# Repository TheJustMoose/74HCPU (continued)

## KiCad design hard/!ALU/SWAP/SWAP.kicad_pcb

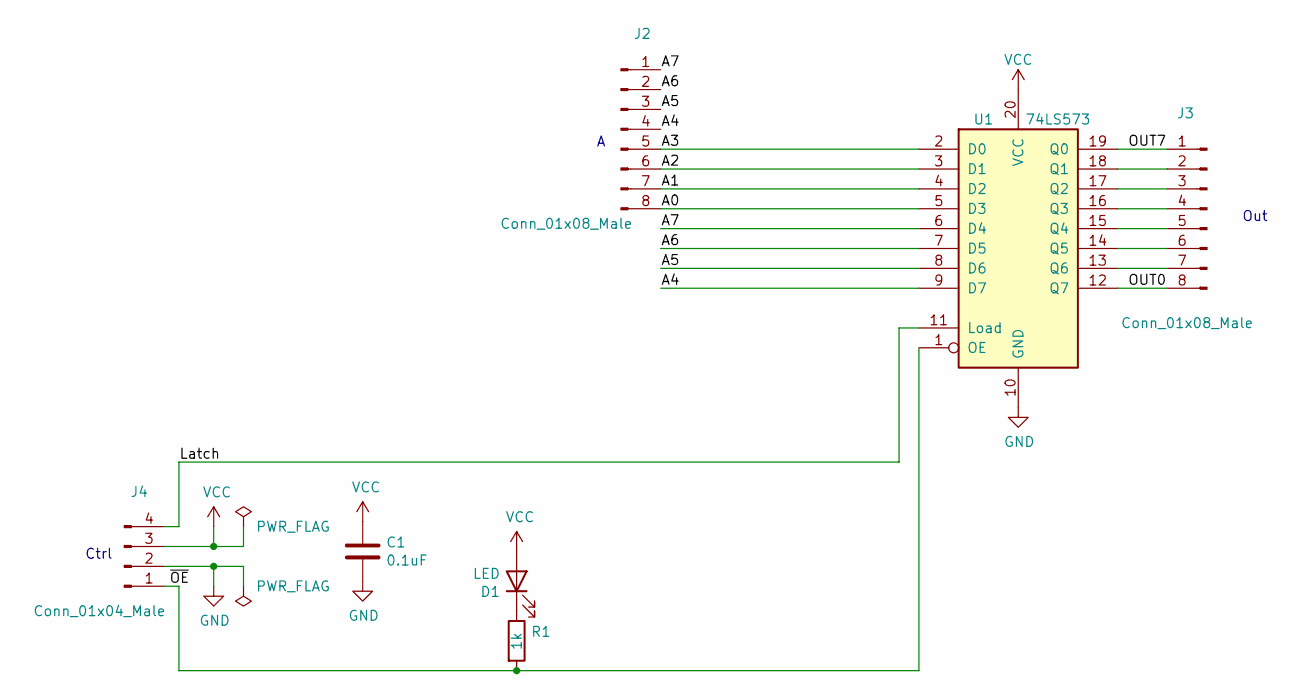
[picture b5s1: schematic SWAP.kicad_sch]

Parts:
C1: 0.1uF; C_0805_2012Metric_Pad1.18x1.45mm_HandSolder
D1: LED; LED_0805_2012Metric_Pad1.15x1.40mm_HandSolder
J2, J3: Conn_01x08_Male; PinHeader_1x08_P2.54mm_Horizontal
J4: Conn_01x04_Male; PinHeader_1x04_P2.54mm_Horizontal
R1: 1k; R_0805_2012Metric_Pad1.20x1.40mm_HandSolder
U1: 74LS573; SOP-20_7.5x12.8mm_P1.27mm

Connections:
/A0: J2.8, U1.5 (D3)
/A1: J2.7, U1.4 (D2)
/A2: J2.6, U1.3 (D1)
/A3: J2.5, U1.2 (D0)
/A4: J2.4, U1.9 (D7)
/A5: J2.3, U1.8 (D6)
/A6: J2.2, U1.7 (D5)
/A7: J2.1, U1.6 (D4)
/Latch: J4.4, U1.11 (Load)
/OUT0: J3.8, U1.12 (Q7)
/OUT7: J3.1, U1.19 (Q0)
/~OE: J4.1, R1.2, U1.1 (OE)
GND: C1.2, J4.2, U1.10 (GND)
unnamed: D1.1 (K), R1.1
unnamed: J3.2, U1.18 (Q1)
unnamed: J3.3, U1.17 (Q2)
unnamed: J3.4, U1.16 (Q3)
unnamed: J3.5, U1.15 (Q4)
unnamed: J3.6, U1.14 (Q5)
unnamed: J3.7, U1.13 (Q6)
VCC: C1.1, D1.2 (A), J4.3, U1.20 (VCC)

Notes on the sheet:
Out
Ctrl

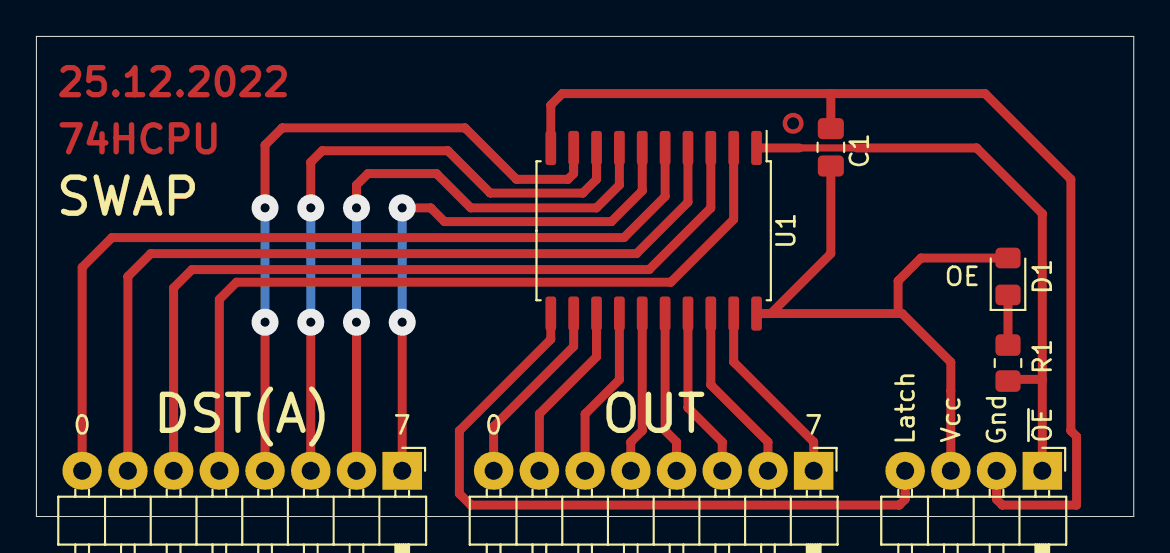
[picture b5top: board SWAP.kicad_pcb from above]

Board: 2 copper layers, 61.0 x 26.7 mm, 7 parts (0 on the bottom side), 21 nets.

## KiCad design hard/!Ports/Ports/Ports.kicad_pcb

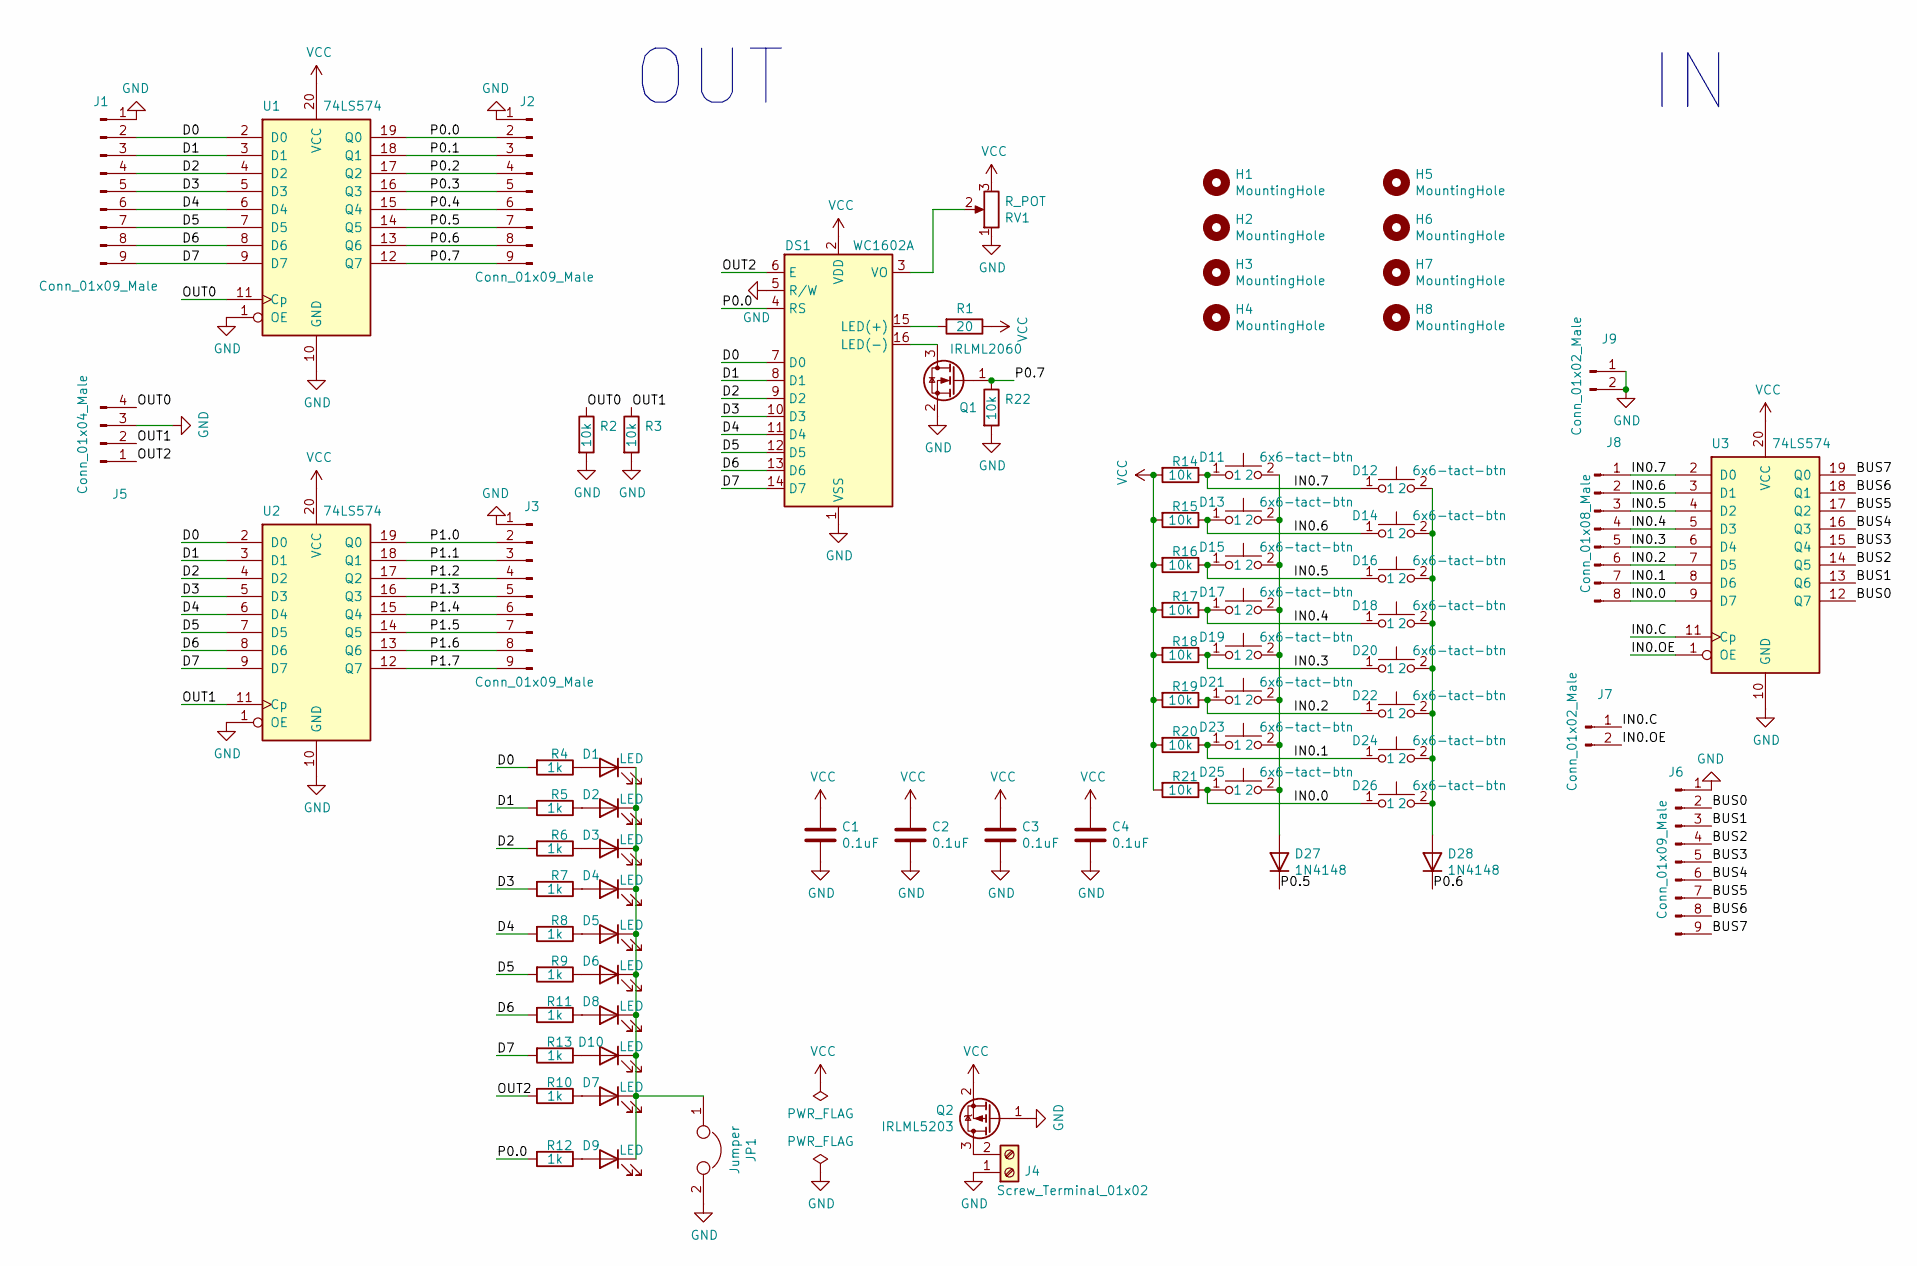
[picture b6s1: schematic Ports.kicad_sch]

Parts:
C1, C2, C3: 0.1uF; C_Axial_L3.8mm_D2.6mm_P22.86mm_Horizontal
C4: 0.1uF; C_Disc_D7.0mm_W2.5mm_P5.00mm
D1, D2, D3, D4, D5, D6, D7, D8, D9, D10: LED; LED_Rectangular_W5.0mm_H2.0mm
D11, D12, D13, D14, D15, D16, D17, D18, D19, D20, D21, D22, D23, D24, D25, D26: 6x6-tact-btn; SW_PUSH_6mm_H4.3mm
D27, D28: 1N4148; D_DO-35_SOD27_P10.16mm_Horizontal
DS1: WC1602A; WH1602-2-holes
H1, H2, H3, H4, H5, H6, H7, H8: MountingHole; MountingHole_3.2mm_M3
J1, J2, J3, J6: Conn_01x09_Male; PinHeader_1x09_P2.54mm_Vertical
J4: Screw_Terminal_01x02; TerminalBlock_Phoenix_PT-1,5-2-5.0-H_1x02_P5.00mm_Horizontal
J5: Conn_01x04_Male; PinHeader_1x04_P2.54mm_Vertical
J7, J9: Conn_01x02_Male; PinHeader_1x02_P2.54mm_Vertical
J8: Conn_01x08_Male; PinHeader_1x08_P2.54mm_Vertical
JP1: Jumper; SolderJumper-2_P1.3mm_Open_RoundedPad1.0x1.5mm
Q1: IRLML2060; SOT-23
Q2: IRLML5203; SOT-23
R1: 20; R_Axial_DIN0207_L6.3mm_D2.5mm_P15.24mm_Horizontal
R2, R3, R14, R15, R16, R17, R18, R19, R20, R21, R22: 10k; R_0805_2012Metric_Pad1.20x1.40mm_HandSolder
R4, R5, R6, R7, R8, R9, R10, R11, R12, R13: 1k; R_0805_2012Metric_Pad1.20x1.40mm_HandSolder
RV1: R_POT; pot-5x5
U1, U2, U3: 74LS574; DIP-20_W7.62mm

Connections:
/BUS0: J6.2, U3.12 (Q7)
/BUS1: J6.3, U3.13 (Q6)
/BUS2: J6.4, U3.14 (Q5)
/BUS3: J6.5, U3.15 (Q4)
/BUS4: J6.6, U3.16 (Q3)
/BUS5: J6.7, U3.17 (Q2)
/BUS6: J6.8, U3.18 (Q1)
/BUS7: J6.9, U3.19 (Q0)
/D0: DS1.7 (D0), J1.2, R4.2, U1.2 (D0), U2.2 (D0)
/D1: DS1.8 (D1), J1.3, R5.2, U1.3 (D1), U2.3 (D1)
/D2: DS1.9 (D2), J1.4, R6.2, U1.4 (D2), U2.4 (D2)
/D3: DS1.10 (D3), J1.5, R7.2, U1.5 (D3), U2.5 (D3)
/D4: DS1.11 (D4), J1.6, R8.2, U1.6 (D4), U2.6 (D4)
/D5: DS1.12 (D5), J1.7, R9.2, U1.7 (D5), U2.7 (D5)
/D6: DS1.13 (D6), J1.8, R11.2, U1.8 (D6), U2.8 (D6)
/D7: DS1.14 (D7), J1.9, R13.2, U1.9 (D7), U2.9 (D7)
/IN0.0: D25.1, D26.1, J8.8, R21.1, U3.9 (D7)
/IN0.1: D23.1, D24.1, J8.7, R20.1, U3.8 (D6)
/IN0.2: D21.1, D22.1, J8.6, R19.1, U3.7 (D5)
/IN0.3: D19.1, D20.1, J8.5, R18.1, U3.6 (D4)
/IN0.4: D17.1, D18.1, J8.4, R17.1, U3.5 (D3)
/IN0.5: D15.1, D16.1, J8.3, R16.1, U3.4 (D2)
/IN0.6: D13.1, D14.1, J8.2, R15.1, U3.3 (D1)
/IN0.7: D11.1, D12.1, J8.1, R14.1, U3.2 (D0)
/IN0.C: J7.1, U3.11 (Cp)
/IN0.OE: J7.2, U3.1 (OE)
/OUT0: J5.4, R2.1, U1.11 (Cp)
/OUT1: J5.2, R3.1, U2.11 (Cp)
/OUT2: DS1.6 (E), J5.1, R10.2
/P0.0: DS1.4 (RS), J2.2, R12.2, U1.19 (Q0)
/P0.1: J2.3, U1.18 (Q1)
/P0.2: J2.4, U1.17 (Q2)
/P0.3: J2.5, U1.16 (Q3)
/P0.4: J2.6, U1.15 (Q4)
/P0.5: D27.1 (K), J2.7, U1.14 (Q5)
/P0.6: D28.1 (K), J2.8, U1.13 (Q6)
/P0.7: J2.9, Q1.1 (G), R22.1, U1.12 (Q7)
/P1.0: J3.2, U2.19 (Q0)
/P1.1: J3.3, U2.18 (Q1)
/P1.2: J3.4, U2.17 (Q2)
/P1.3: J3.5, U2.16 (Q3)
/P1.4: J3.6, U2.15 (Q4)
/P1.5: J3.7, U2.14 (Q5)
/P1.6: J3.8, U2.13 (Q6)
/P1.7: J3.9, U2.12 (Q7)
GND: C1.2, C2.2, C3.2, C4.2, DS1.1 (VSS), DS1.5 (R/W), J1.1, J2.1, J3.1, J4.1, J5.3, J6.1, J9.1, J9.2, JP1.2, Q1.2 (S), Q2.1 (G), R2.2, R3.2, R22.2, RV1.1, U1.1 (OE), U1.10 (GND), U2.1 (OE), U2.10 (GND), U3.10 (GND)
unnamed: D1.1 (K), D2.1 (K), D3.1 (K), D4.1 (K), D5.1 (K), D6.1 (K), D7.1 (K), D8.1 (K), D9.1 (K), D10.1 (K), JP1.1
unnamed: D1.2 (A), R4.1
unnamed: D2.2 (A), R5.1
unnamed: D3.2 (A), R6.1
unnamed: D4.2 (A), R7.1
unnamed: D5.2 (A), R8.1
unnamed: D6.2 (A), R9.1
unnamed: D7.2 (A), R10.1
unnamed: D8.2 (A), R11.1
unnamed: D9.2 (A), R12.1
unnamed: D10.2 (A), R13.1
unnamed: D11.2, D13.2, D15.2, D17.2, D19.2, D21.2, D23.2, D25.2, D27.2 (A)
unnamed: D12.2, D14.2, D16.2, D18.2, D20.2, D22.2, D24.2, D26.2, D28.2 (A)
unnamed: DS1.3 (VO), RV1.2
unnamed: DS1.15 (LED(+)), R1.2
unnamed: DS1.16 (LED(-)), Q1.3 (D)
unnamed: J4.2, Q2.3 (D)
VCC: C1.1, C2.1, C3.1, C4.1, DS1.2 (VDD), Q2.2 (S), R1.1, R14.2, R15.2, R16.2, R17.2, R18.2, R19.2, R20.2, R21.2, RV1.3, U1.20 (VCC), U2.20 (VCC), U3.20 (VCC)

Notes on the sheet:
OUT

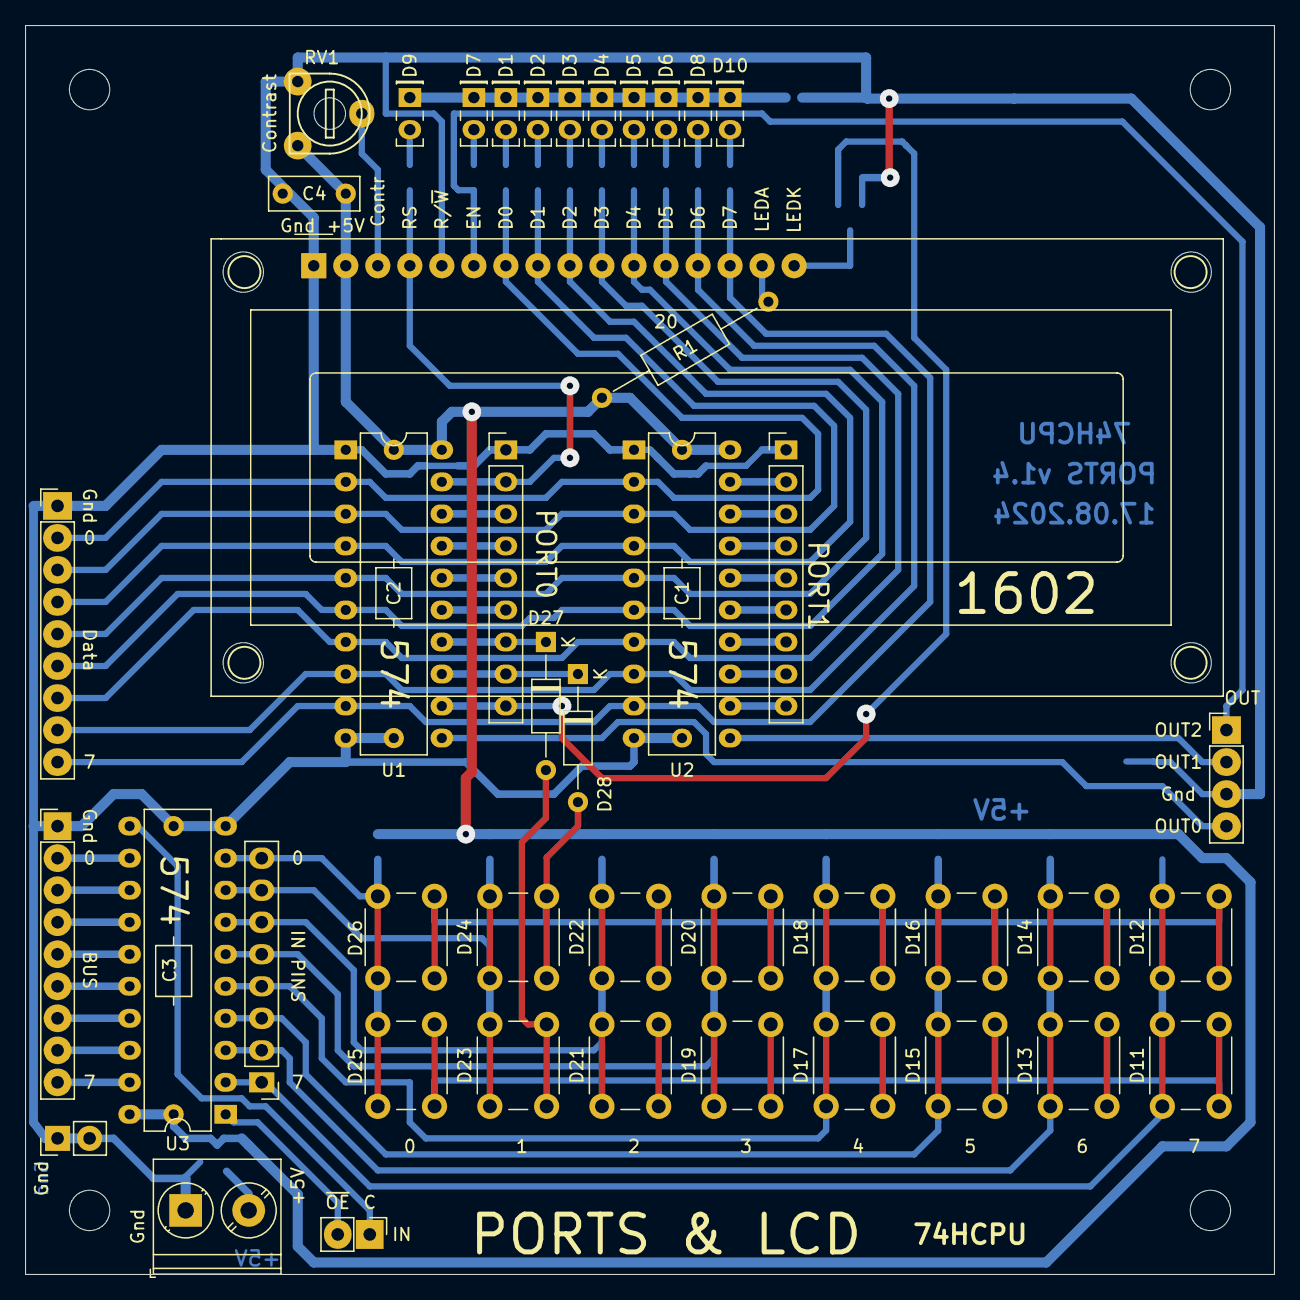
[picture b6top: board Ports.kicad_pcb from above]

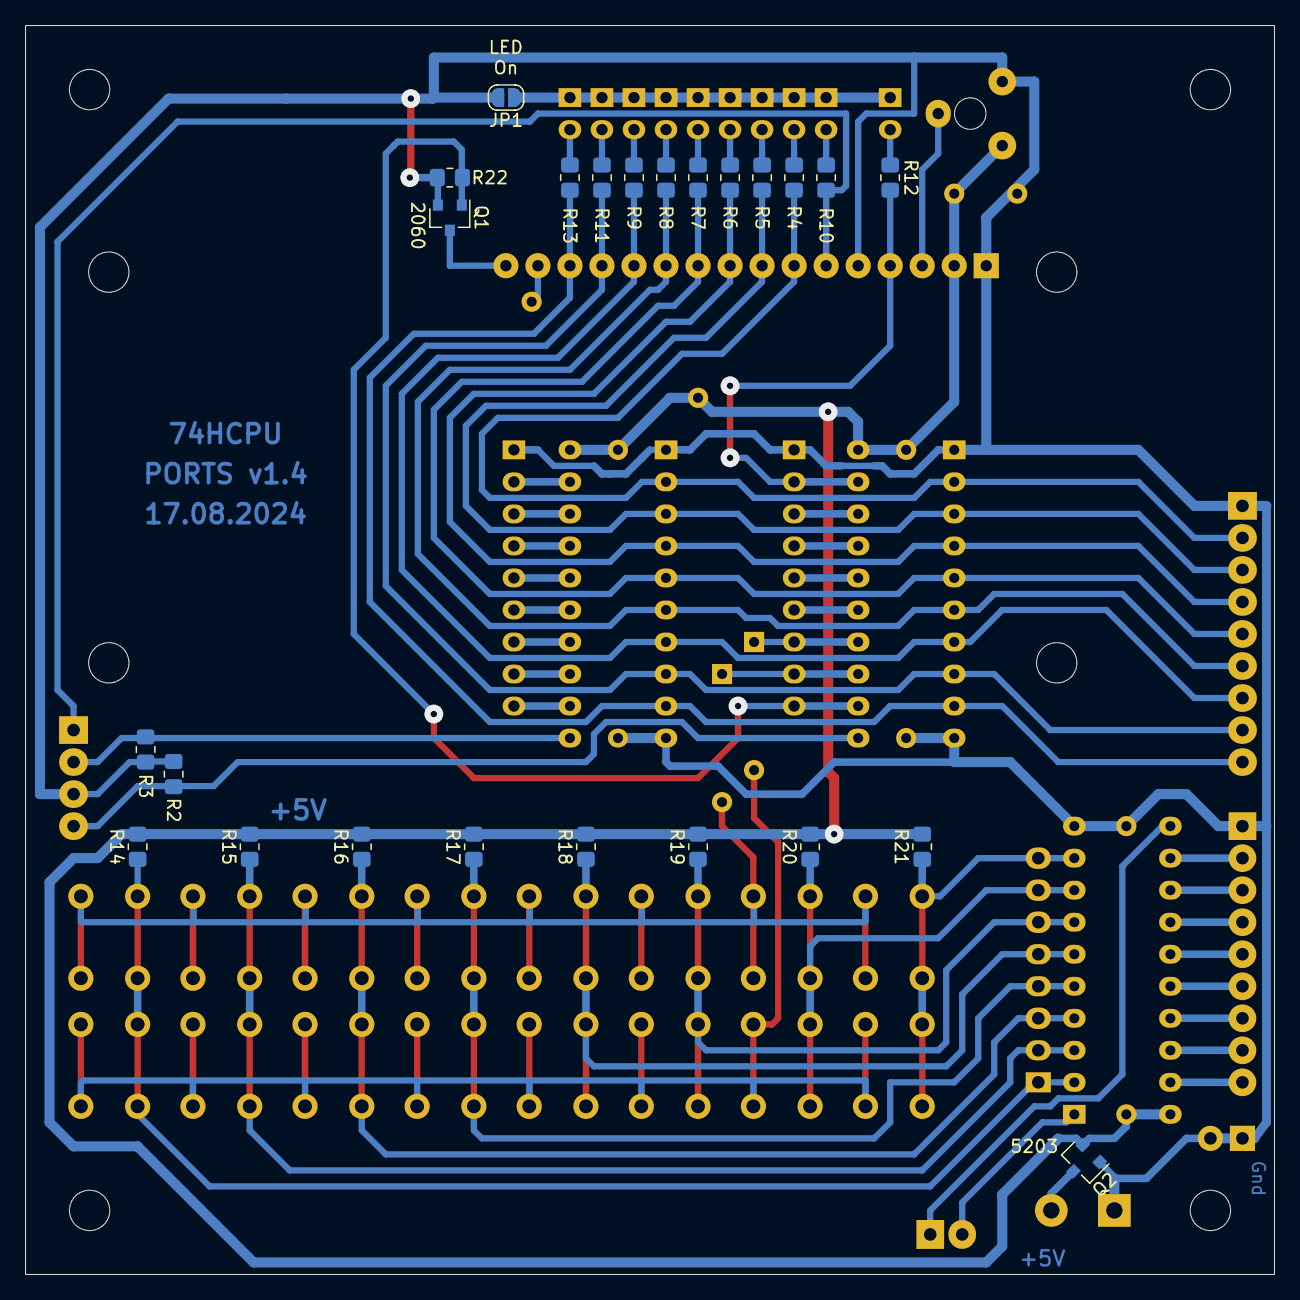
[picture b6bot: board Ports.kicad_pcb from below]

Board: 2 copper layers, 99.1 x 99.1 mm, 79 parts (24 on the bottom side), 64 nets.

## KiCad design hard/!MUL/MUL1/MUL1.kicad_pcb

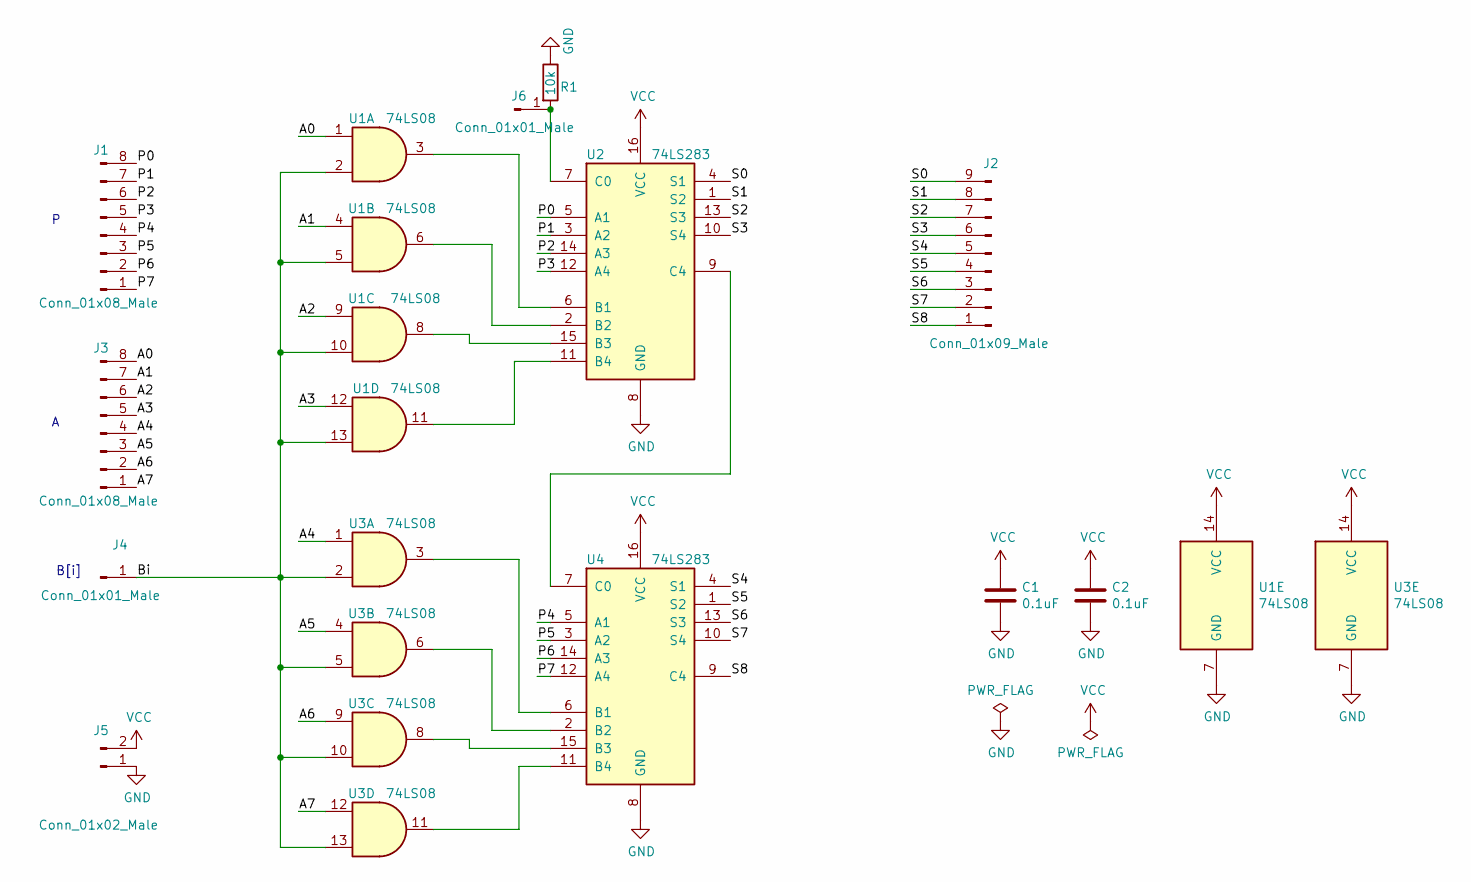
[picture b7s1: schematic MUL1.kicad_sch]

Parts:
C1, C2: 0.1uF; C_Disc_D7.5mm_W5.0mm_P10.00mm
J1, J3: Conn_01x08_Male; PinHeader_1x08_P2.54mm_Horizontal
J2: Conn_01x09_Male; PinHeader_1x09_P2.54mm_Horizontal
J4: Conn_01x01_Male; PinHeader_1x01_P2.54mm_Horizontal
J5: Conn_01x02_Male; PinHeader_1x02_P2.54mm_Horizontal
J6: Conn_01x01_Male; PinHeader_1x01_P2.54mm_Vertical
R1: 10k; R_0805_2012Metric_Pad1.20x1.40mm_HandSolder
U1, U3: 74LS08; DIP-14_W7.62mm_Socket
U2, U4: 74LS283; DIP-16_W7.62mm_Socket

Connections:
/A0: J3.8, U1.1
/A1: J3.7, U1.4
/A2: J3.6, U1.9
/A3: J3.5, U1.12
/A4: J3.4, U3.1
/A5: J3.3, U3.4
/A6: J3.2, U3.9
/A7: J3.1, U3.12
/Bi: J4.1, U1.2, U1.5, U1.10, U1.13, U3.2, U3.5, U3.10, U3.13
/P0: J1.8, U2.5 (A1)
/P1: J1.7, U2.3 (A2)
/P2: J1.6, U2.14 (A3)
/P3: J1.5, U2.12 (A4)
/P4: J1.4, U4.5 (A1)
/P5: J1.3, U4.3 (A2)
/P6: J1.2, U4.14 (A3)
/P7: J1.1, U4.12 (A4)
/S0: J2.9, U2.4 (S1)
/S1: J2.8, U2.1 (S2)
/S2: J2.7, U2.13 (S3)
/S3: J2.6, U2.10 (S4)
/S4: J2.5, U4.4 (S1)
/S5: J2.4, U4.1 (S2)
/S6: J2.3, U4.13 (S3)
/S7: J2.2, U4.10 (S4)
/S8: J2.1, U4.9 (C4)
GND: C1.2, C2.2, J5.1, R1.1, U1.7 (GND), U2.8 (GND), U3.7 (GND), U4.8 (GND)
unnamed: J6.1, R1.2, U2.7 (C0)
unnamed: U1.3, U2.6 (B1)
unnamed: U1.6, U2.2 (B2)
unnamed: U1.8, U2.15 (B3)
unnamed: U1.11, U2.11 (B4)
unnamed: U2.9 (C4), U4.7 (C0)
unnamed: U3.3, U4.6 (B1)
unnamed: U3.6, U4.2 (B2)
unnamed: U3.8, U4.15 (B3)
unnamed: U3.11, U4.11 (B4)
VCC: C1.1, C2.1, J5.2, U1.14 (VCC), U2.16 (VCC), U3.14 (VCC), U4.16 (VCC)

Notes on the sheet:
B[i]

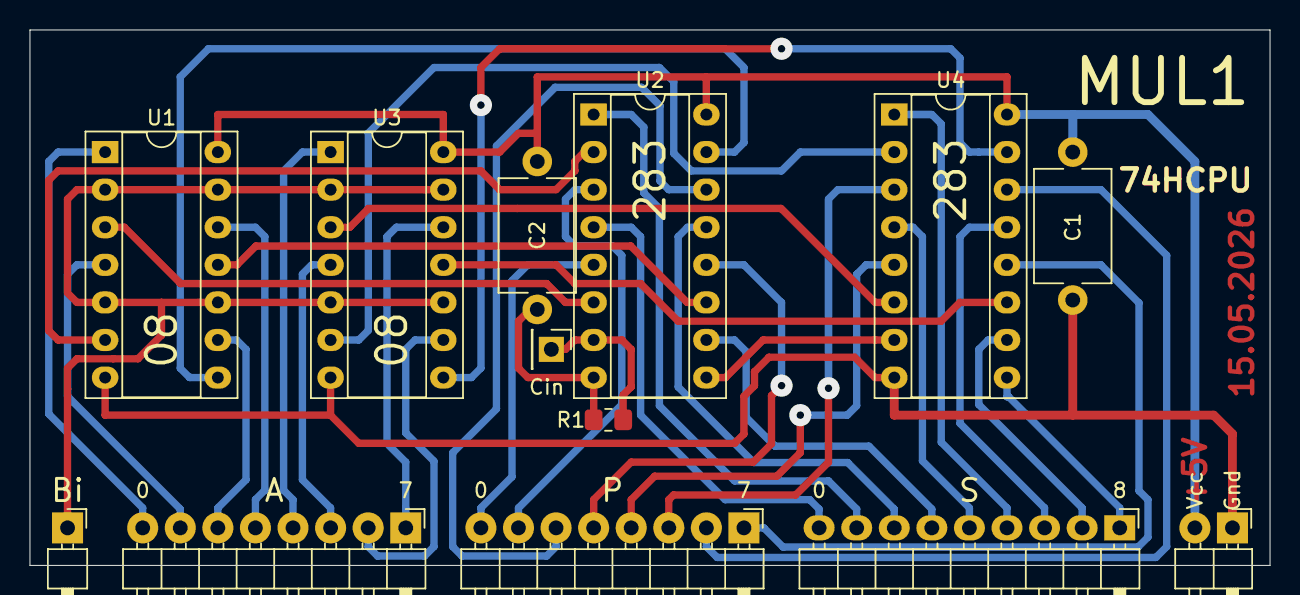
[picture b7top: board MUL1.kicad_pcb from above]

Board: 2 copper layers, 83.8 x 36.2 mm, 13 parts (0 on the bottom side), 38 nets.

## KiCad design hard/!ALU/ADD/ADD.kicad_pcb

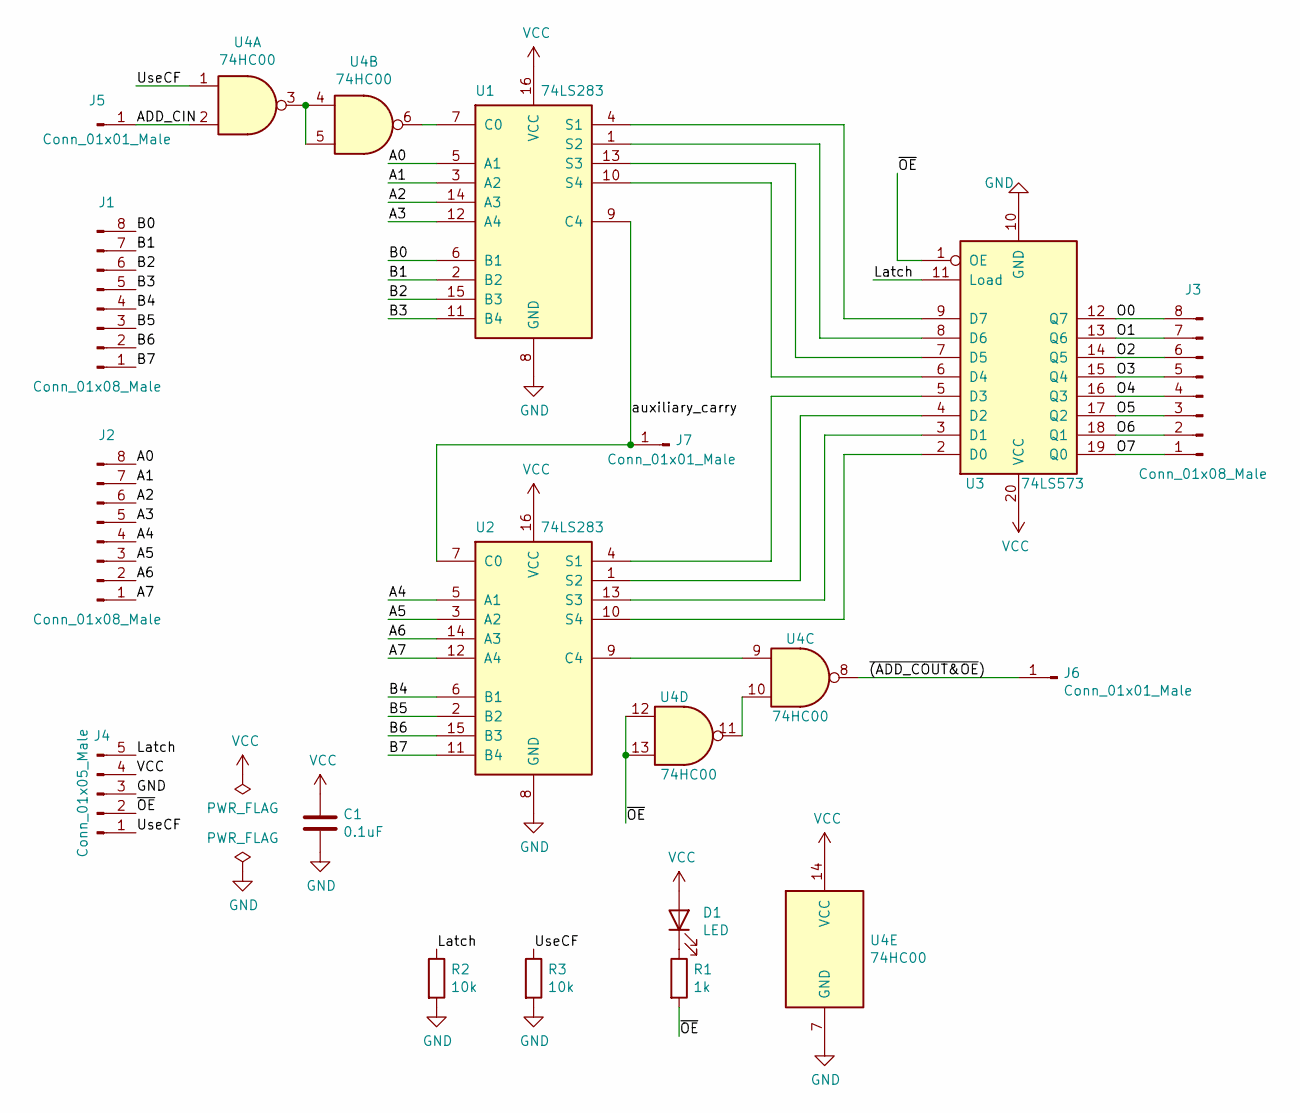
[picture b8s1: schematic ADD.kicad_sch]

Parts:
C1: 0.1uF; C_0805_2012Metric_Pad1.18x1.45mm_HandSolder
D1: LED; LED_0805_2012Metric_Pad1.15x1.40mm_HandSolder
J1, J2, J3: Conn_01x08_Male; PinHeader_1x08_P2.54mm_Horizontal
J4: Conn_01x05_Male; PinHeader_1x05_P2.54mm_Horizontal
J5, J6, J7: Conn_01x01_Male; PinHeader_1x01_P2.54mm_Vertical
R1: 1k; R_0805_2012Metric_Pad1.20x1.40mm_HandSolder
R2, R3: 10k; R_0805_2012Metric_Pad1.20x1.40mm_HandSolder
U1, U2: 74LS283; DIP-16_W7.62mm
U3: 74LS573; DIP-20_W7.62mm
U4: 74HC00; DIP-14_W7.62mm

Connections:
/A0: J2.8, U1.5 (A1)
/A1: J2.7, U1.3 (A2)
/A2: J2.6, U1.14 (A3)
/A3: J2.5, U1.12 (A4)
/A4: J2.4, U2.5 (A1)
/A5: J2.3, U2.3 (A2)
/A6: J2.2, U2.14 (A3)
/A7: J2.1, U2.12 (A4)
/ADD_CIN: J5.1, U4.2
/B0: J1.8, U1.6 (B1)
/B1: J1.7, U1.2 (B2)
/B2: J1.6, U1.15 (B3)
/B3: J1.5, U1.11 (B4)
/B4: J1.4, U2.6 (B1)
/B5: J1.3, U2.2 (B2)
/B6: J1.2, U2.15 (B3)
/B7: J1.1, U2.11 (B4)
/Latch: J4.5, R2.1, U3.11 (Load)
/O0: J3.8, U3.12 (Q7)
/O1: J3.7, U3.13 (Q6)
/O2: J3.6, U3.14 (Q5)
/O3: J3.5, U3.15 (Q4)
/O4: J3.4, U3.16 (Q3)
/O5: J3.3, U3.17 (Q2)
/O6: J3.2, U3.18 (Q1)
/O7: J3.1, U3.19 (Q0)
/UseCF: J4.1, R3.1, U4.1
/auxiliary_carry: J7.1, U1.9 (C4), U2.7 (C0)
/~(ADD_COUT&OE): J6.1, U4.8
/~OE: J4.2, R1.2, U3.1 (OE), U4.12, U4.13
GND: C1.2, J4.3, R2.2, R3.2, U1.8 (GND), U2.8 (GND), U3.10 (GND), U4.7 (GND)
unnamed: D1.1 (K), R1.1
unnamed: U1.7 (C0), U4.6
unnamed: U1.4 (S1), U3.9 (D7)
unnamed: U1.1 (S2), U3.8 (D6)
unnamed: U1.13 (S3), U3.7 (D5)
unnamed: U1.10 (S4), U3.6 (D4)
unnamed: U2.9 (C4), U4.9
unnamed: U2.4 (S1), U3.5 (D3)
unnamed: U2.1 (S2), U3.4 (D2)
unnamed: U2.13 (S3), U3.3 (D1)
unnamed: U2.10 (S4), U3.2 (D0)
unnamed: U4.3, U4.4, U4.5
unnamed: U4.10, U4.11
VCC: C1.1, D1.2 (A), J4.4, U1.16 (VCC), U2.16 (VCC), U3.20 (VCC), U4.14 (VCC)

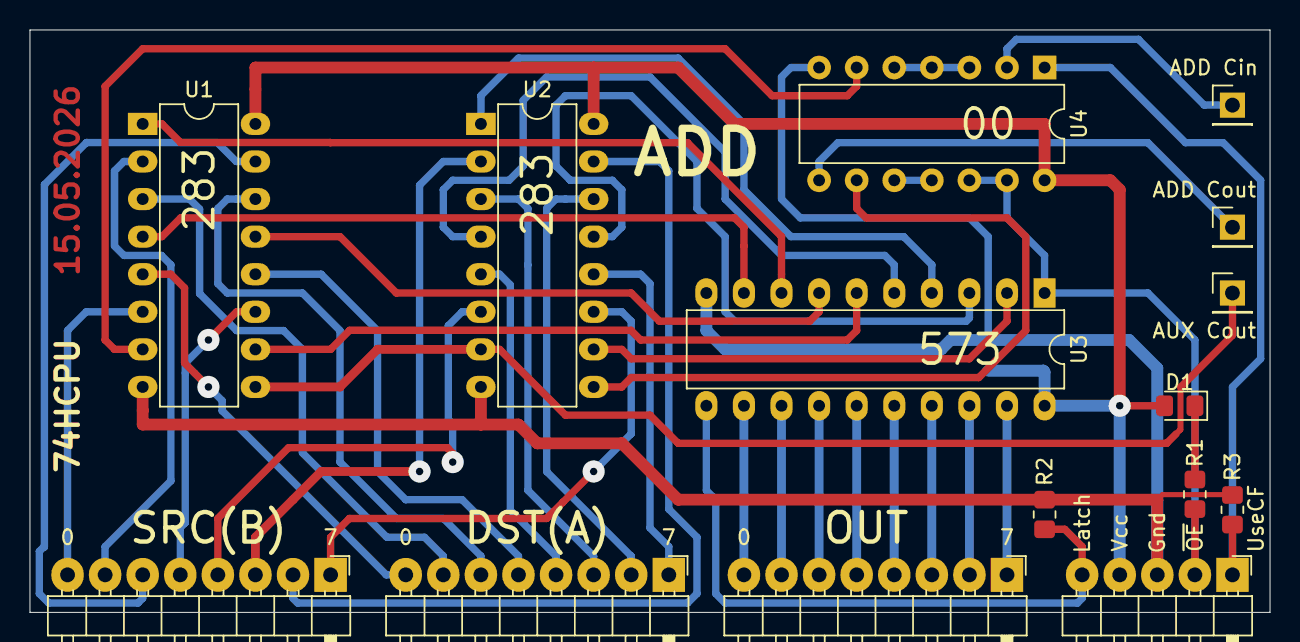
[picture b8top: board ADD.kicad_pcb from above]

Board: 2 copper layers, 83.8 x 39.4 mm, 16 parts (1 on the bottom side), 45 nets.

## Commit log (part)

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2026-02-15 Code to get consts size
2026-02-15 Migrate to GetFirstEmptyWindowWithSize
2026-02-15 Cleanup. Remove OCC from PrintCode
2026-02-15 Try to print consts tables with addresses:
2026-02-16 chmod +x build.sh
2026-02-16 Add submodules init
2026-02-16 Try to add -v (verbose) flag
2026-02-16 Parsing args in work
2026-02-16 Hooray! It works!
2026-02-16 Polishing error reporting
2026-02-16 Width argument for ToHexString
2026-02-16 Add screenshot of ASM
2026-02-16 Add header in .md
2026-02-18 I want to use any addresses, not only string addresses
2026-02-19 Just mistype
2026-02-19 Change index of SP register
2026-02-19 Fix unit tests. Add flag to disable writing debug info
2026-02-19 Try to use char glyph in firmware!
2026-02-20 1251 -> utf-8
2026-02-20 Try to use optional<uint16_t> instead of uint16_t
2026-02-20 Done
2026-02-20 One little change
2026-02-20 Lost error that needs to be printed
2026-02-20 Unit tests have to detect unknown operations
2026-02-20 Replace three methods to one template
2026-02-20 Oops. Lost verbose flag
2026-02-20 Bugfixing. Have to print also warning and messages
2026-02-20 Try to extract ROM routines into separate module
2026-02-21 Polishing CPU structure
2026-02-21 Polishing README.md
2026-02-21 Fix layout of README.md
2026-02-21 One more experiment with MD
2026-02-21 Fix bug in bitset of memory (wrong function in assm.h). Polishing README.md
2026-02-21 Will use SlotAllocator, Assembler will delegate some methods to it
2026-02-21 Just prototype of template
2026-02-21 Polishing SlotAllocator
2026-02-21 Try to use OccupyIt(addr, size) instead of OccupyIt(addr)
2026-02-21 There can be only one
2026-02-22 Regs v6.1
2026-02-23 Regs v6.1 in work
2026-02-24 Small test for names
2026-02-24 Move reg.h upper
2026-02-24 Move flags.h upper
2026-02-24 Fix includes
2026-02-25 Try to minimize expression
2026-02-26 Add dump.lock file because I need cross-platform Mutex
2026-02-27 Try to minimize expression :)
2026-02-27 Simplest expr in work
2026-02-27 Now it can process 1+2 ;)
2026-02-27 Now it can process + and -
2026-02-27 Now it can process numbers instead of digits
2026-02-27 Try to create three address code
2026-02-28 Add unary minus
2026-02-28 Add mul and div. Add logs)
2026-03-01 if -> switch
2026-03-02 In work
2026-03-02 Bugfixing)
2026-03-03 Add equal sign
2026-03-03 I have completely removed the duplicate methods
2026-03-03 Replace if to switch
2026-03-03 Try to add vars and assignments
2026-03-03 Name node in work
2026-03-03 Some old changes
2026-03-03 Add pip install into .bat/.sh
2026-03-03 Assing seems to work!
2026-03-03 Expressions in work
2026-03-04 Try to implement parsing for a=b=c=123
2026-03-04 Polishing
2026-03-04 Try to process many statements
2026-03-05 Lexer in work
2026-03-05 Try to move doctest to common place
2026-03-05 Try to rever parser and move Lexer to separate unit
2026-03-05 Will use cmake instead of clear clang
2026-03-05 Fix lexer, cmake and add tests
2026-03-05 Playing with tests
2026-03-05 Fix first test of Lexer ;)
2026-03-05 We need more tests!!
2026-03-06 Fix bugs, add tests!
2026-03-06 Still in work...
2026-03-07 Just rename of method
2026-03-07 Try to replace many asserts to one loop :)
2026-03-07 Try to replace many asserts to one loop
2026-03-07 Try to test real stmt
2026-03-07 Continue to replace GetToken to currentToken
2026-03-07 Extract Token and NodeType names into separate module
2026-03-07 I home now Lexer works!
2026-03-07 Small clean up
2026-03-08 Remove unused src
2026-03-08 Split one file to many little classes and files
2026-03-08 Just rename
2026-03-08 Build is Ok!
2026-03-08 Moving towards code generation
2026-03-08 Mistype
2026-03-08 Three address code also should store result name
2026-03-08 Now parser can read test from file!
2026-03-08 Polishing printing. Add empty module for optimization
2026-03-08 Crutching
2026-03-08 First optimization of code ;)
2026-03-08 Okay, what about variables declaration?
2026-03-08 Add one variable of one type and without initialization *ROFL*
2026-03-09 Try to add pointers
2026-03-09 Add variable list)
2026-03-09 Remove res() method. Now it's just parser, not calculator ;)
2026-03-10 Regs-v6.1 in work
2026-03-11 Have to check variable existence
2026-03-12 Remove todos from code
2026-03-12 Try to store variable type
2026-03-13 Try to store variable size
2026-03-13 Now var size is available in asm
2026-03-13 Fix bug with lost operation. Add logs.
2026-03-13 Will convert IR to ASM
2026-03-14 Working on convert IR to ASM
2026-03-14 Try to initialize variables during declaration
2026-03-14 Added print error.
2026-03-14 Try to print better
2026-03-15 Fix build
2026-03-15 We need moooreeee files!!
2026-03-15 Parser in work
2026-03-15 Workin on tree print
2026-03-15 Bugfixing
2026-03-15 Debugging print_tree
2026-03-15 Another way to calc offset
2026-03-15 One more try...
2026-03-15 Tree is drawing good ;)
2026-03-15 It works!
2026-03-15 Comment debug strings
2026-03-16 Fix build on Linux
2026-03-16 Restore tmp vars name
2026-03-17 expr in work
2026-03-17 Move methods to header
2026-03-17 Lost class
2026-03-18 Bugfixing expr parser
2026-03-18 Should store type of arithm value
2026-03-18 Regs v6.1 is almost ready!
2026-03-19 Regs v6.1 is ok
2026-03-20 Add variables table and pointer bit
2026-03-21 Try to process pointers
2026-03-22 Remove logs, add comments
2026-03-22 Polishing code
2026-03-23 TODOs
2026-03-23 asm instruction can contain only one number
2026-03-23 Just .gitignore
2026-03-23 Try to allocate registers
2026-03-24 We need mooore todos!!!
2026-03-25 MUX8x1-1bit v2
2026-03-26 MUX8x1-1bit v2 is finished
2026-03-27 Some problem with this files
2026-03-27 MUX8x1-1bit v2 is almost ready
2026-03-27 KiCAD 5 -> 9
2026-03-27 Polishing PCB. Make new gerbers
2026-03-27 Just move MUX PCB to subfolder
2026-03-27 Update gerbers
2026-03-27 End Plate PCB for Registers
2026-03-27 Some lost file from MUX8x1-1bit
2026-03-28 MUX8x1-1bit v2 rework
2026-03-28 End Plate PCB in work
2026-03-28 Lost file in MUX8x1-1bit
2026-03-29 Fix build script
2026-03-30 MUX8x1-1bit v2 is ready
2026-03-30 End Plate: make a circuit corresponding to the multiplexers
2026-03-30 End Plate in work
2026-03-30 End Plate polishing
2026-03-30 Move gerbers to subfolder
2026-03-31 Some file from MUX8x1-1bit pcb
2026-04-02 Fix build. Move fuction to class in expr
2026-04-02 Extract RegsBank into separate module
2026-04-02 Unit tests for RegsBank will be here
2026-04-02 Testing RegsBank...
2026-04-02 One more unit test for RegsBank0
2026-04-02 Add trompeloeil to check methods call
2026-04-02 Add trompeloeil to project settings
2026-04-02 Try to extract Spill method to separate interface
2026-04-02 First mock test is Ok!
2026-04-03 Polishing unit tests
2026-04-03 Process variable declaration
2026-04-03 Prepare to use variables table
2026-04-05 Small changes
2026-04-05 Rename assemble.* -> backend.*
2026-04-05 Rename Assemble -> GenerateCode
2026-04-05 Now it's class
2026-04-05 GenerateCode in work
2026-04-05 Try to connect variables to Spill method
2026-04-05 Extract method
2026-04-05 Extract one more method
2026-04-05 Extract last method
2026-04-05 Fix margins
2026-04-06 Polishing Backend class
2026-04-06 Try to separate code and comments
2026-04-08 Backend in work
2026-04-08 Remove unused param
2026-04-08 Spill method in work
2026-04-09 Happy moment when it works
2026-04-09 Still work
2026-04-09 Add some logging for Spill
2026-04-09 Polishing Spill
2026-04-10 Playing with Spill()
2026-04-10 Polishing code output
2026-04-10 Swap instruction and comment
2026-04-10 Small fixes
2026-04-10 Now source code is printed as comment after instruction
2026-04-11 Testing md layout
2026-04-11 It wasn't md. Add instruction descriptions
2026-04-11 Polishing instruction descriptions
2026-04-11 Oops
2026-04-11 Bugfixing in Spill method
2026-04-11 Polishing, bugfixing, etc...
2026-04-12 Try to display live variables
2026-04-12 Fix printing unary node
2026-04-12 Adding data_type field into Node
2026-04-12 Try to use data_type() everywhere
2026-04-13 Polishing printing live variables. Remove comments
2026-04-14 More methods for RegsBank
2026-04-14 Try to use live&dead variables
2026-04-15 Fill is pair to Spill
2026-04-15 Remove junk file. Remove 'res' arg from methods
2026-04-15 Okay, Fill method works
2026-04-17 EndPlate pcb polishing
2026-05-01 Fix silk
2026-05-01 Cut EndPlate PCB
2026-05-01 MUX8x1 gerbers
2026-05-02 Lost file for Regs v6.1
2026-05-02 EndPlate gerbers
2026-05-02 MUX8x1-1bit gerbers
2026-05-03 Move some code to function compile
2026-05-03 Switch columns in table
2026-05-03 Try to remove duplicate code
2026-05-03 Refactoring *ROFL*
2026-05-03 Extract methods
2026-05-04 File is not required
2026-05-04 Try to create SMD version of MUL1
2026-05-06 2 DIP and 2 SO!
2026-05-06 Polishing after review
2026-05-06 assert -> throw exception
2026-05-06 Have to check dynamic_cast result
2026-05-06 lost return res
2026-05-07 Try to replace raw ptr to unique_ptr
2026-05-07 Another exception
2026-05-07 Add grammar description
2026-05-11 Extract vars to separate module
2026-05-11 Continue processing variables
2026-05-12 Try to use Visitor pattern
2026-05-12 set DataType to Vars
2026-05-12 Add vars initialization
2026-05-13 Generate code of var initialization
2026-05-13 Lost catch
2026-05-13 Convert magic value into std::optional
2026-05-13 Bugfixing. Should use one instruction with immediate instead of two instructions
2026-05-14 Some lost file from AND_SMD pcb
2026-05-14 Some lost file from ADD pcb
2026-05-15 Polishing MUL
2026-05-15 .gitignore
2026-05-15 Polishing ADD
2026-05-15 Polishing MUL1
2026-05-15 ALU in work
2026-05-15 Replace AND/OR/XOR/MOV on proper symbol
2026-05-15 Polishing ALU
2026-05-24 Previous version is not required
2026-05-24 Line on Silk is not required!
2026-05-27 Extract visitor to header
2026-05-27 Fix storing of is_num flag
2026-05-28 Extract EnumTree class to separate module
2026-06-04 Add code collector interface
2026-06-04 Move code generation into Visitor
2026-06-04 Some lost changes
2026-06-17 Lost call
2026-06-17 make the print narrower
2026-06-17 Try to use one dir for cmake & vsc
2026-06-17 Clean up
2026-06-21 Add relational operations to grammar
2026-06-21 Add while and logical operations to grammar
2026-06-21 Semicolon must finish statement
2026-06-21 Add if...else to grammar
2026-06-21 Add bitwise operations to grammar
2026-06-21 Add functions to grammar
2026-06-21 Add return operator to grammar, move var declarations to top
2026-06-21 Add comments, rename name_list in grammar
2026-06-21 Add dereference and get address to grammar
2026-06-21 Add post-increment of vars to grammar
2026-06-21 Now function can return nothing!
2026-06-23 Unit tests for Parser
2026-06-23 New tokens for lexer
2026-06-23 Just comment logs
2026-06-23 Add AddressOf operator
2026-06-23 Fix printing. Add unit test for address_of
2026-06-24 Rename UnOp. Small fixes
2026-06-24 Dereference operator in work
2026-06-24 Oops. Wrong banks!
2026-06-24 Reverse the order of grammar rules
2026-06-24 Refactoring
2026-06-24 Just functions
2026-06-25 Creating relational operations
2026-06-25 Tmp var for comparison result
2026-06-25 Fix printing AST
2026-06-26 We need more visitors
2026-06-26 Check args in relative op
2026-06-26 One more rename
2026-06-26 Rename vars
2026-06-27 Add new Node, remove param name
2026-06-27 Sort by alphabetical order
2026-06-27 Sort by alphabetical order, add lost declaration
2026-06-27 Equal and Assign are two different operations
2026-06-27 Comparison operator in work
2026-06-27 One more keyword of type
2026-06-27 We need more tokens
2026-06-27 Rename params, fix cmnt string
2026-06-27 struct -> class
2026-06-27 Now Operation has type
2026-06-27 Relational operations in work
2026-06-27 Add if keyword
2026-06-28 If statement in work
2026-06-28 Bugfixing: lost consume()
2026-06-28 Fix Lexer
2026-06-29 Add operation type to Operation class
2026-06-29 More logs...
2026-06-29 Fix table width
2026-06-29 Implementing if code generating
2026-06-29 If statement works
2026-06-29 Add else keyword
2026-06-29 Remove not required conditions
2026-06-29 Polishing while condition
2026-06-29 Try to check lexer tokens
2026-06-29 Bugfixing!
2026-06-29 Add else keyword processing
